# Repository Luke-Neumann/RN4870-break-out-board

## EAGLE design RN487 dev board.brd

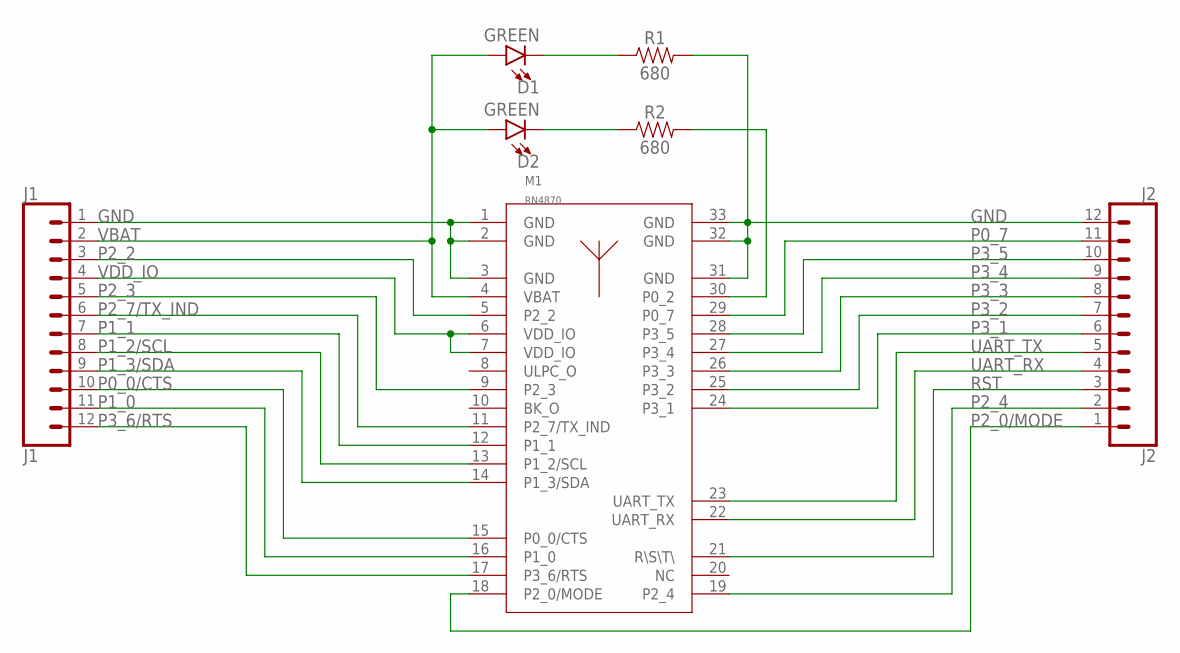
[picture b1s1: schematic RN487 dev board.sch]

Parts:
D1, D2: GREEN; LED-0603
J1: J1; 1X12
J2: J2; 1X12
M1: RN4870
R1, R2: 680; 0603

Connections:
GND: J1.1, J2.12, M1.1 (GND), M1.2 (GND), M1.3 (GND), M1.31 (GND), M1.32 (GND), M1.33 (GND), R1.2
unnamed: D2.C, R2.1
unnamed: D1.C, R1.1
unnamed: M1.30 (P0_2), R2.2
P0_0/CTS: J1.10, M1.15 (P0_0/CTS)
P0_7: J2.11, M1.29 (P0_7)
P1_0: J1.11, M1.16 (P1_0)
P1_1: J1.7, M1.12 (P1_1)
P1_2/SCL: J1.8, M1.13 (P1_2/SCL)
P1_3/SDA: J1.9, M1.14 (P1_3/SDA)
P2_0/MODE: J2.1, M1.18 (P2_0/MODE)
P2_2: J1.3, M1.5 (P2_2)
P2_3: J1.5, M1.9 (P2_3)
P2_4: J2.2, M1.19 (P2_4)
P2_7/TX_IND: J1.6, M1.11 (P2_7/TX_IND)
P3_1: J2.6, M1.24 (P3_1)
P3_2: J2.7, M1.25 (P3_2)
P3_3: J2.8, M1.26 (P3_3)
P3_4: J2.9, M1.27 (P3_4)
P3_5: J2.10, M1.28 (P3_5)
P3_6/RTS: J1.12, M1.17 (P3_6/RTS)
RST: J2.3, M1.21 (R\S\T\)
UART_RX: J2.4, M1.22 (UART_RX)
UART_TX: J2.5, M1.23 (UART_TX)
VBAT: D1.A, D2.A, J1.2, M1.4 (VBAT)
VDD_IO: J1.4, M1.6 (VDD_IO), M1.7 (VDD_IO)

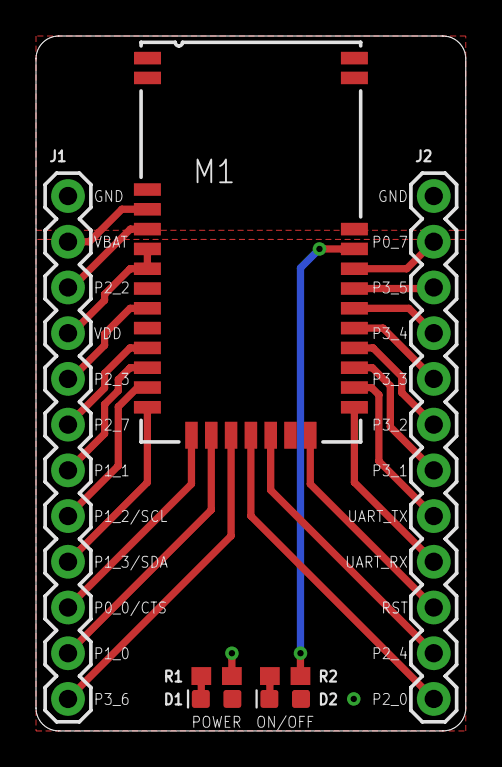
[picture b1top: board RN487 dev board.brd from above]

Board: 4 copper layers, 23.9 x 38.6 mm, 7 parts (0 on the bottom side), 26 nets.

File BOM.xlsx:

Part | Value | digikey # | Device | Package | Description | PROD_ID | VALUE
D1 | GREEN | 516-2493-1-ND | LED-GREEN0603 | LED-0603 | Green SMD LED | DIO-00821 | GREEN
D2 | GREEN | 516-2493-1-ND | LED-GREEN0603 | LED-0603 | Green SMD LED | DIO-00821 | GREEN
J1 | J1 | 2057-PH1-12-UA-ND | CONN_12 | 1X12 | Multi connection point. Often used as Generic Header-pin footprint for 0.1 inch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
J2 | J2 | 2057-PH1-12-UA-ND | CONN_12 | 1X12 | Multi connection point. Often used as Generic Header-pin footprint for 0.1 inch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
M1 | RN4870 |  | RN4870-I/RM130 | RN4870
R1 | 680 | P680GCT-ND | 680OHM-0603-1/10W-5% | 603 | 680Œ© resistor | RES-09333 | 680
R2 | 680 | P680GCT-ND | 680OHM-0603-1/10W-5% | 603 | 680Œ© resistor | RES-09333 | 680

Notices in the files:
parts and their libraries:
SparkFun-Connectors: Licensing: Creative Commons ShareAlike 4.0 International - https://creativecommons.org/licenses/by-sa/4.0
